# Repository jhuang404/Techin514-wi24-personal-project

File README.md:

# Techin514-wi24-personal-project
)
.png)
.png)
.png)
https://blog.csdn.net/weixin_33582089/article/details/143576077?ops_request_misc=&request_id=&biz_id=102&utm_term=%E8%BF%90%E5%8A%A8%E6%A3%80%E6%B5%8Bmpu6050&utm_medium=distribute.pc_search_result.none-task-blog-2~all~sobaiduweb~default-4-143576077.142^v101^pc_search_result_base9&spm=1018.2226.3001.4187
https://blog.csdn.net/xddwg521125/article/details/136511404?ops_request_misc=&request_id=&biz_id=102&utm_term=%E8%BF%90%E5%8A%A8%E6%A3%80%E6%B5%8Bmpu6050&utm_medium=distribute.pc_search_result.none-task-blog-2~all~sobaiduweb~default-7-136511404.142^v101^pc_search_result_base9&spm=1018.2226.3001.4187
https://blog.csdn.net/qq_45682974/article/details/127889831?ops_request_misc=&request_id=&biz_id=102&utm_term=%E8%BF%90%E5%8A%A8%E6%A3%80%E6%B5%8Bmpu6050&utm_medium=distribute.pc_search_result.none-task-blog-2~all~sobaiduweb~default-9-127889831.142^v101^pc_search_result_base9&spm=1018.2226.3001.4187
https://blog.csdn.net/weixin_47730988/article/details/135740980?ops_request_misc=&request_id=&biz_id=102&utm_term=%E8%BF%90%E5%8A%A8%E6%A3%80%E6%B5%8Bmpu6050&utm_medium=distribute.pc_search_result.none-task-blog-2~all~sobaiduweb~default-0-135740980.142^v101^pc_search_result_base9&spm=1018.2226.3001.4187
https://blog.csdn.net/weixin_47730988/article/details/135740980?ops_request_misc=&request_id=&biz_id=102&utm_term=%E8%BF%90%E5%8A%A8%E6%A3%80%E6%B5%8Bmpu6050&utm_medium=distribute.pc_search_result.none-task-blog-2~all~sobaiduweb~default-0-135740980.142^v101^pc_search_result_base9&spm=1018.2226.3001.4187

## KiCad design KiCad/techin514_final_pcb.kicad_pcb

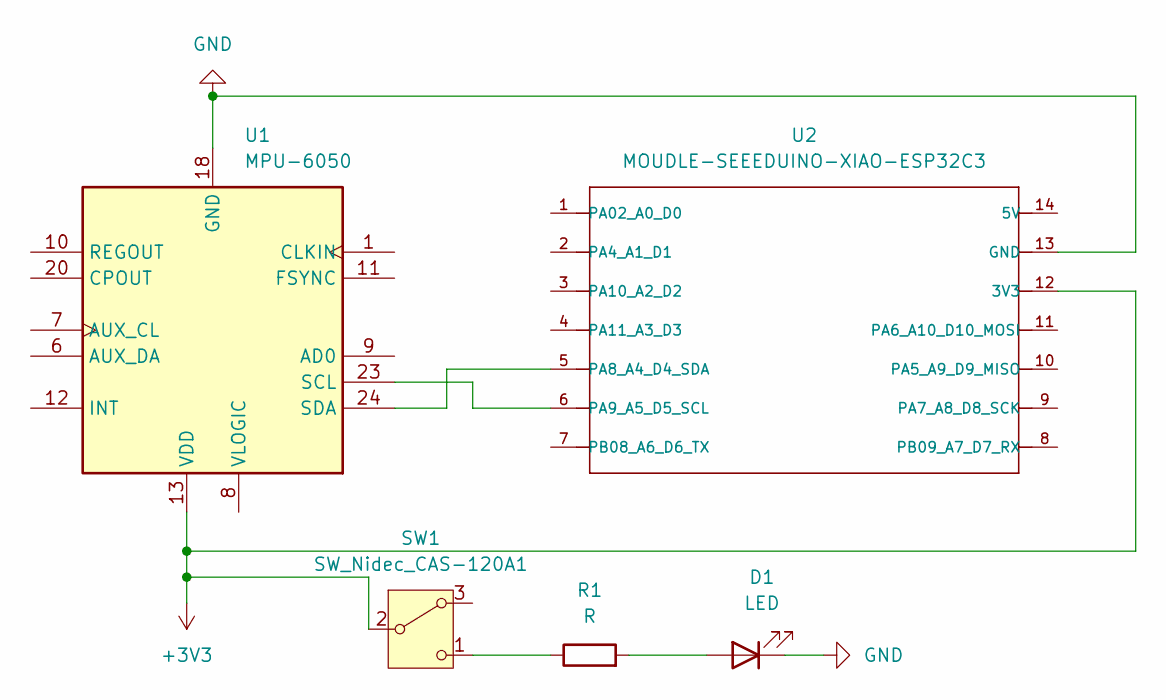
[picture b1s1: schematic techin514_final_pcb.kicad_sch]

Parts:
D1: LED; LED_0201_0603Metric
R1: R; R_0201_0603Metric
SW1: SW_Nidec_CAS-120A1; Nidec_Copal_CAS-120A
U1: MPU-6050; InvenSense_QFN-24_4x4mm_P0.5mm
U2: MOUDLE-SEEEDUINO-XIAO-ESP32C3; MOUDLE14P-SMD-2.54-21X17.8MM

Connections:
+3V3: SW1.2 (B), U1.13 (VDD), U2.12 (3V3)
GND: D1.1 (K), U1.18 (GND), U2.13 (GND)
unnamed: D1.2 (A), R1.2
unnamed: R1.1, SW1.1 (C)
unnamed: U1.23 (SCL), U2.6 (PA9_A5_D5_SCL)
unnamed: U1.24 (SDA), U2.5 (PA8_A4_D4_SDA)

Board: 2 copper layers, 5 parts (0 on the bottom side), 6 nets, no tracks yet.

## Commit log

2025-01-22 Create images
2025-01-22 Create datasheet
2025-01-22 Update and rename datasheet to website
2025-02-14 Rename Datasheet.pdf to Battery Datasheet.pdf
